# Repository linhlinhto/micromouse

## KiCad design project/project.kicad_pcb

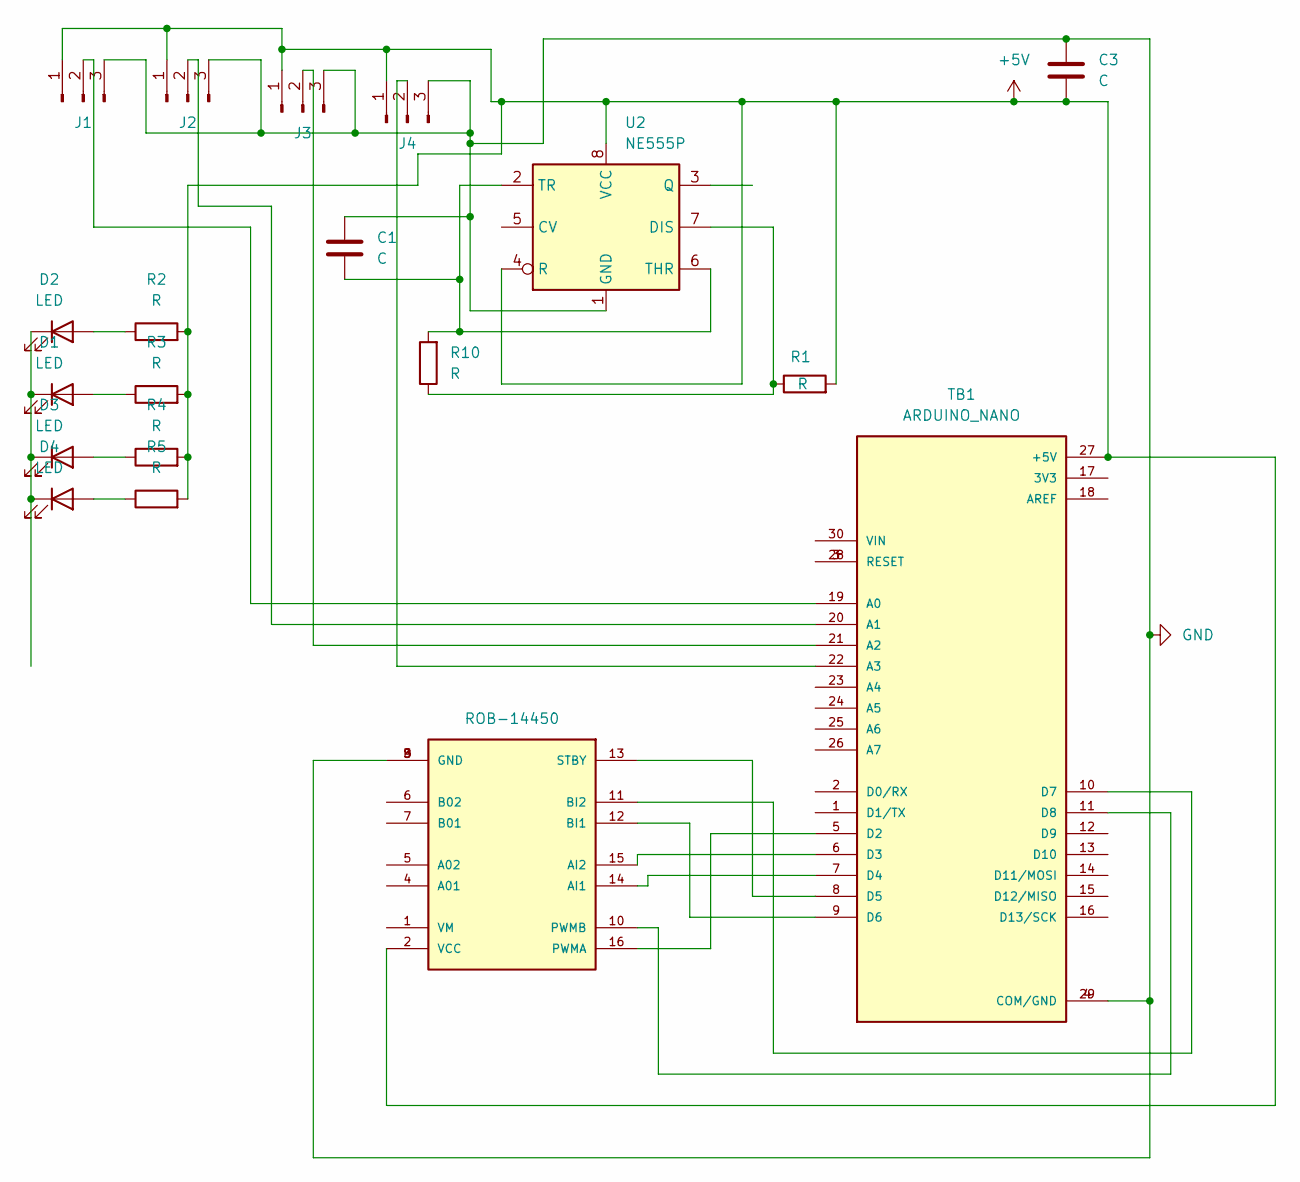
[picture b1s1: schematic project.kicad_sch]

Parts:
C1, C3: C; C_0805_2012Metric
D1, D2, D3, D4: LED; LED_D5.0mm
J1, J2, J3, J4: Conn_01x03_Pin; PinSocket_1x03_P2.00mm_Vertical
R1, R2, R3, R4, R5, R10: R; R_0805_2012Metric
TB1: ARDUINO_NANO; Arduino_Nano
U2: NE555P; DIP-8_W7.62mm
U4: ROB-14450; TB6612FNG; PARTREV 11-13-17

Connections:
+5V: C3.1, J1.1, J2.1, J3.1, J4.1, R1.2, R2.2, R3.2, R4.2, R5.2, TB1.27 (+5V), U2.4 (R), U2.8 (VCC), U4.2 (VCC)
GND: C1.2, C3.2, J1.3, J2.3, J3.3, J4.3, TB1.4 (COM/GND), TB1.29 (COM/GND), U2.1 (GND), U4.3 (GND), U4.8 (GND), U4.9 (GND)
unnamed: D1.2 (A), R3.1
unnamed: D1.1 (K), D2.1 (K), D3.1 (K), D4.1 (K)
unnamed: D2.2 (A), R2.1
unnamed: D3.2 (A), R4.1
unnamed: D4.2 (A), R5.1
unnamed: J1.2, TB1.19 (A0)
unnamed: J2.2, TB1.20 (A1)
unnamed: J3.2, TB1.21 (A2)
unnamed: J4.2, TB1.22 (A3)
unnamed: TB1.5 (D2), U4.16 (PWMA)
unnamed: TB1.6 (D3), U4.15 (AI2)
unnamed: TB1.7 (D4), U4.14 (AI1)
unnamed: TB1.8 (D5), U4.13 (STBY)
unnamed: TB1.9 (D6), U4.12 (BI1)
unnamed: TB1.10 (D7), U4.11 (BI2)
unnamed: TB1.11 (D8), U4.10 (PWMB)
unnamed: TB1.3 (RESET), TB1.28 (RESET)
unnamed: R1.1, R10.1, U2.7 (DIS)
unnamed: C1.1, R10.2, U2.2 (TR), U2.6 (THR)

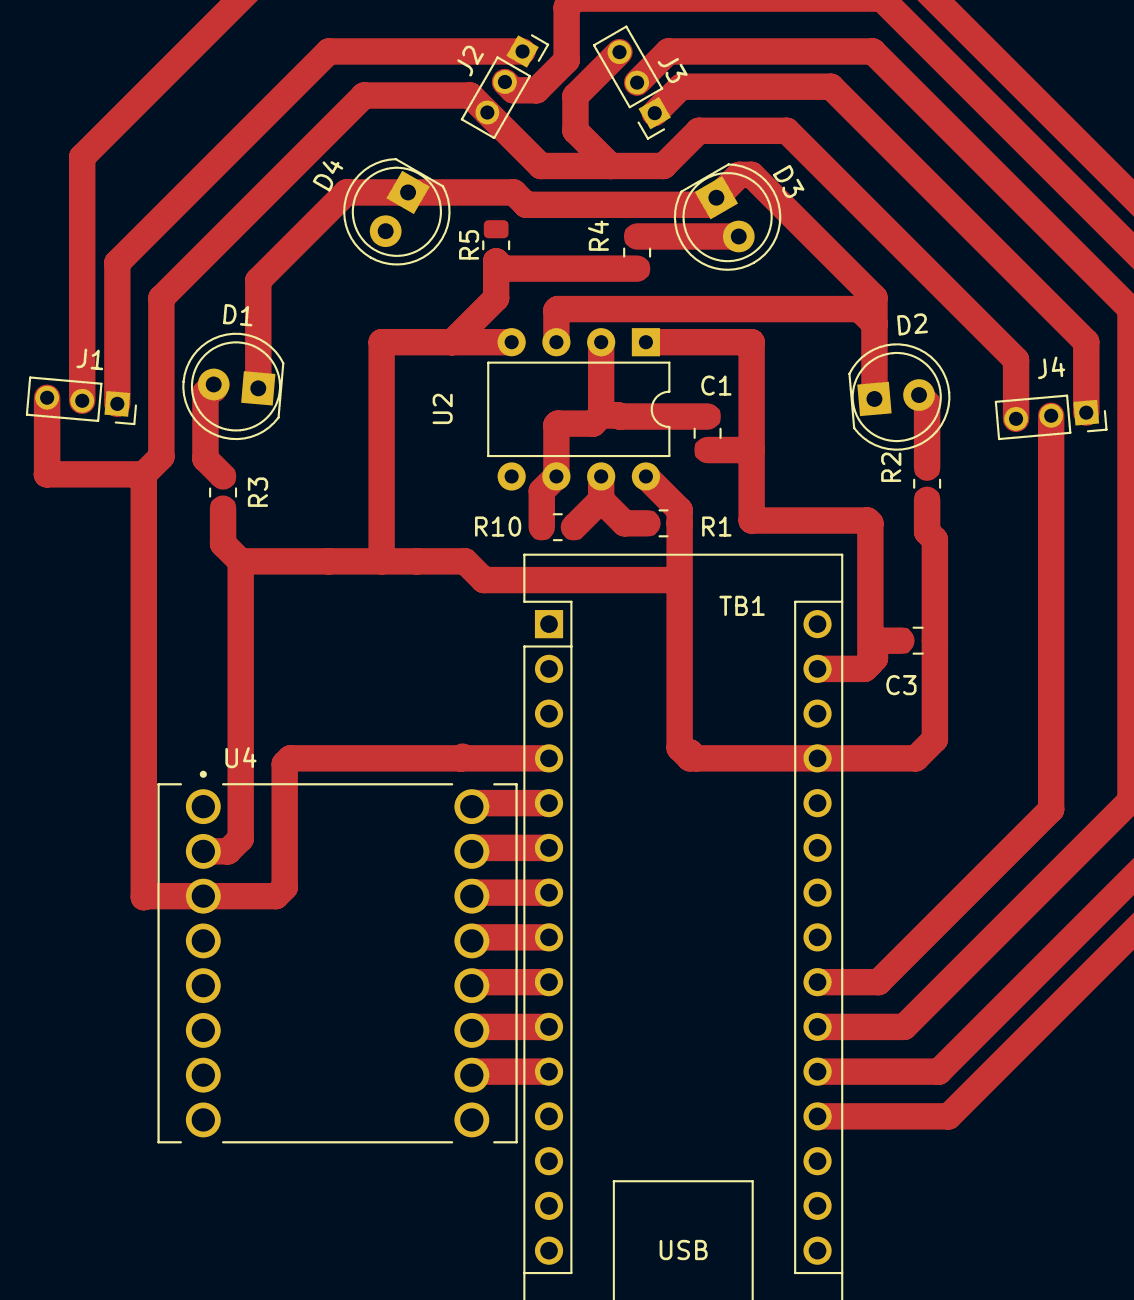
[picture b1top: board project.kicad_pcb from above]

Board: 2 copper layers, 19 parts (0 on the bottom side), 21 nets.

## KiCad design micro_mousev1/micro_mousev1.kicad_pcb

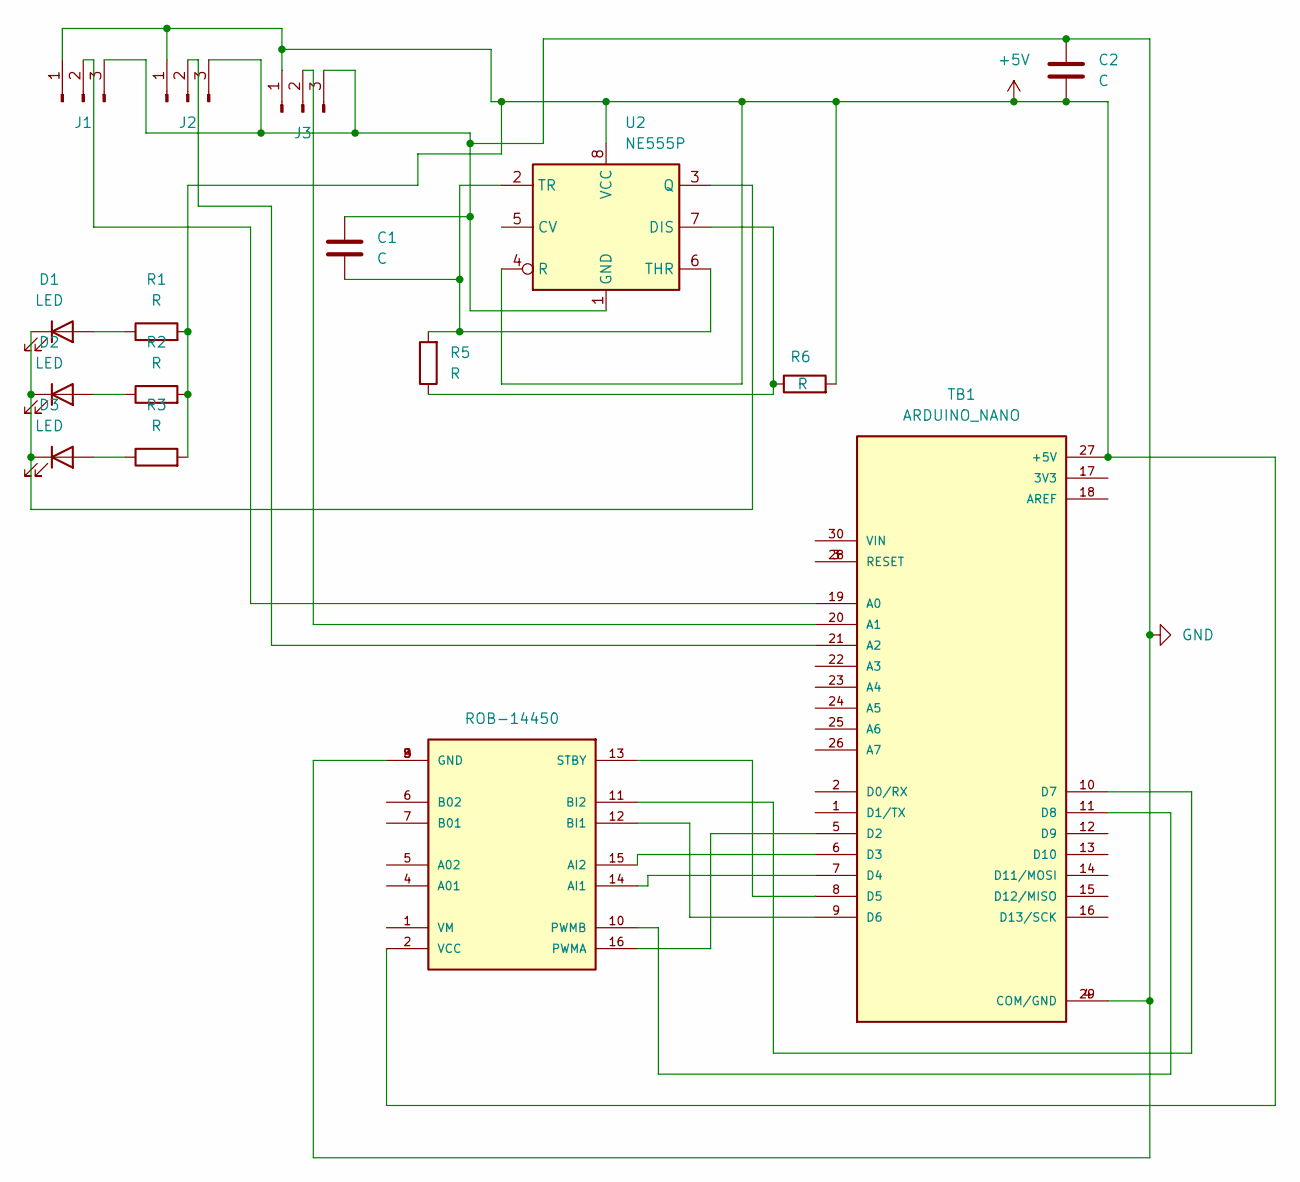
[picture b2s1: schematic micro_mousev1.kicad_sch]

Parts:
C1, C2: C; C_0805_2012Metric
D1, D2, D3: LED; LED_D5.0mm
J1, J2, J3: Conn_01x03_Pin; PinSocket_1x03_P2.00mm_Vertical
R1, R2, R3, R5, R6: R; R_0805_2012Metric
TB1: ARDUINO_NANO; Arduino_Nano
U1: ROB-14450; tb6612; PARTREV 11-13-17
U2: NE555P; DIP-8_W7.62mm

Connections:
+5V: C2.1, J1.1, J2.1, J3.1, R1.2, R2.2, R3.2, R6.2, TB1.27 (+5V), U1.2 (VCC), U2.4 (R), U2.8 (VCC)
GND: C1.2, C2.2, J1.3, J2.3, J3.3, TB1.4 (COM/GND), TB1.29 (COM/GND), U1.3 (GND), U1.8 (GND), U1.9 (GND), U2.1 (GND)
unnamed: D1.2 (A), R1.1
unnamed: D1.1 (K), D2.1 (K), D3.1 (K), U2.3 (Q)
unnamed: D2.2 (A), R2.1
unnamed: D3.2 (A), R3.1
unnamed: J1.2, TB1.19 (A0)
unnamed: J2.2, TB1.21 (A2)
unnamed: J3.2, TB1.20 (A1)
unnamed: TB1.5 (D2), U1.16 (PWMA)
unnamed: TB1.6 (D3), U1.15 (AI2)
unnamed: TB1.7 (D4), U1.14 (AI1)
unnamed: TB1.8 (D5), U1.13 (STBY)
unnamed: TB1.9 (D6), U1.12 (BI1)
unnamed: TB1.10 (D7), U1.11 (BI2)
unnamed: TB1.11 (D8), U1.10 (PWMB)
unnamed: TB1.3 (RESET), TB1.28 (RESET)
unnamed: R5.1, R6.1, U2.7 (DIS)
unnamed: C1.1, R5.2, U2.2 (TR), U2.6 (THR)

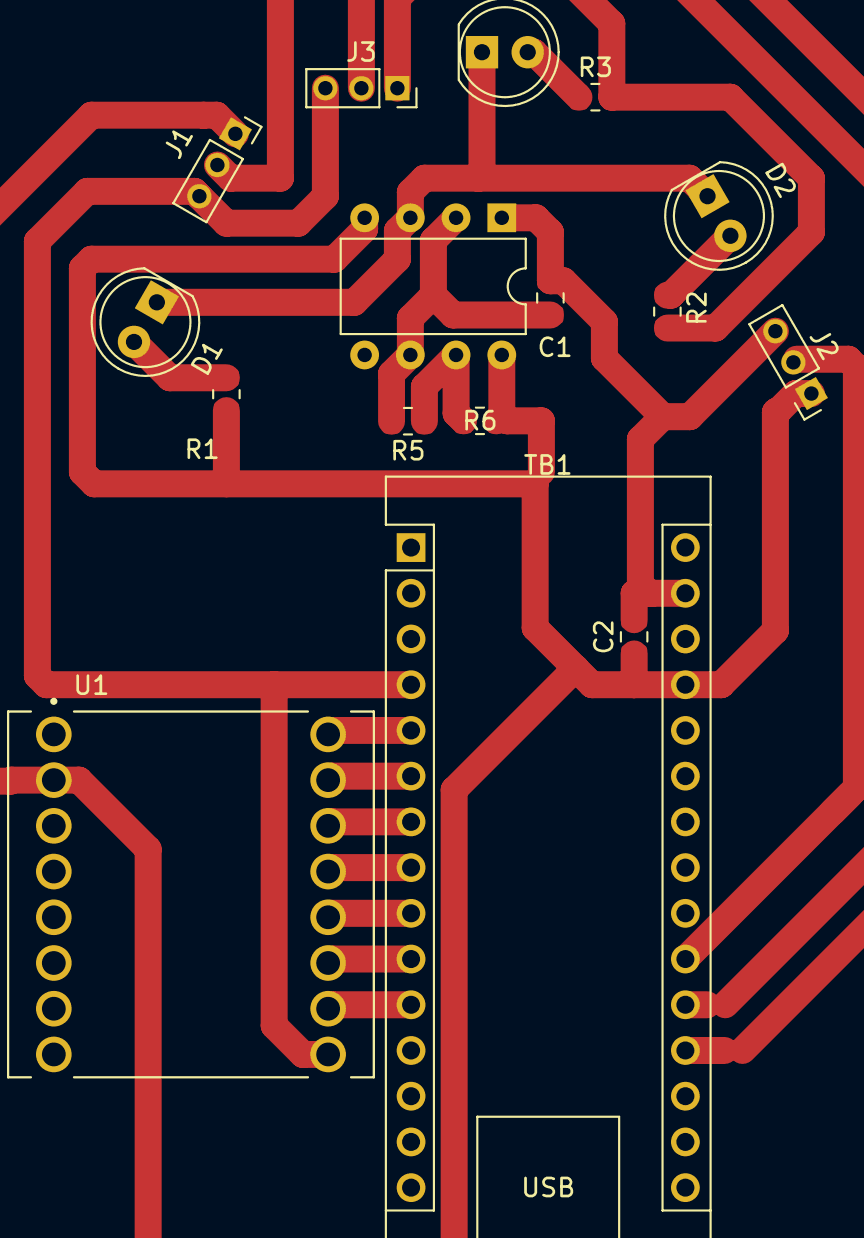
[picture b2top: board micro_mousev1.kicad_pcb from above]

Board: 2 copper layers, 16 parts (0 on the bottom side), 19 nets.
